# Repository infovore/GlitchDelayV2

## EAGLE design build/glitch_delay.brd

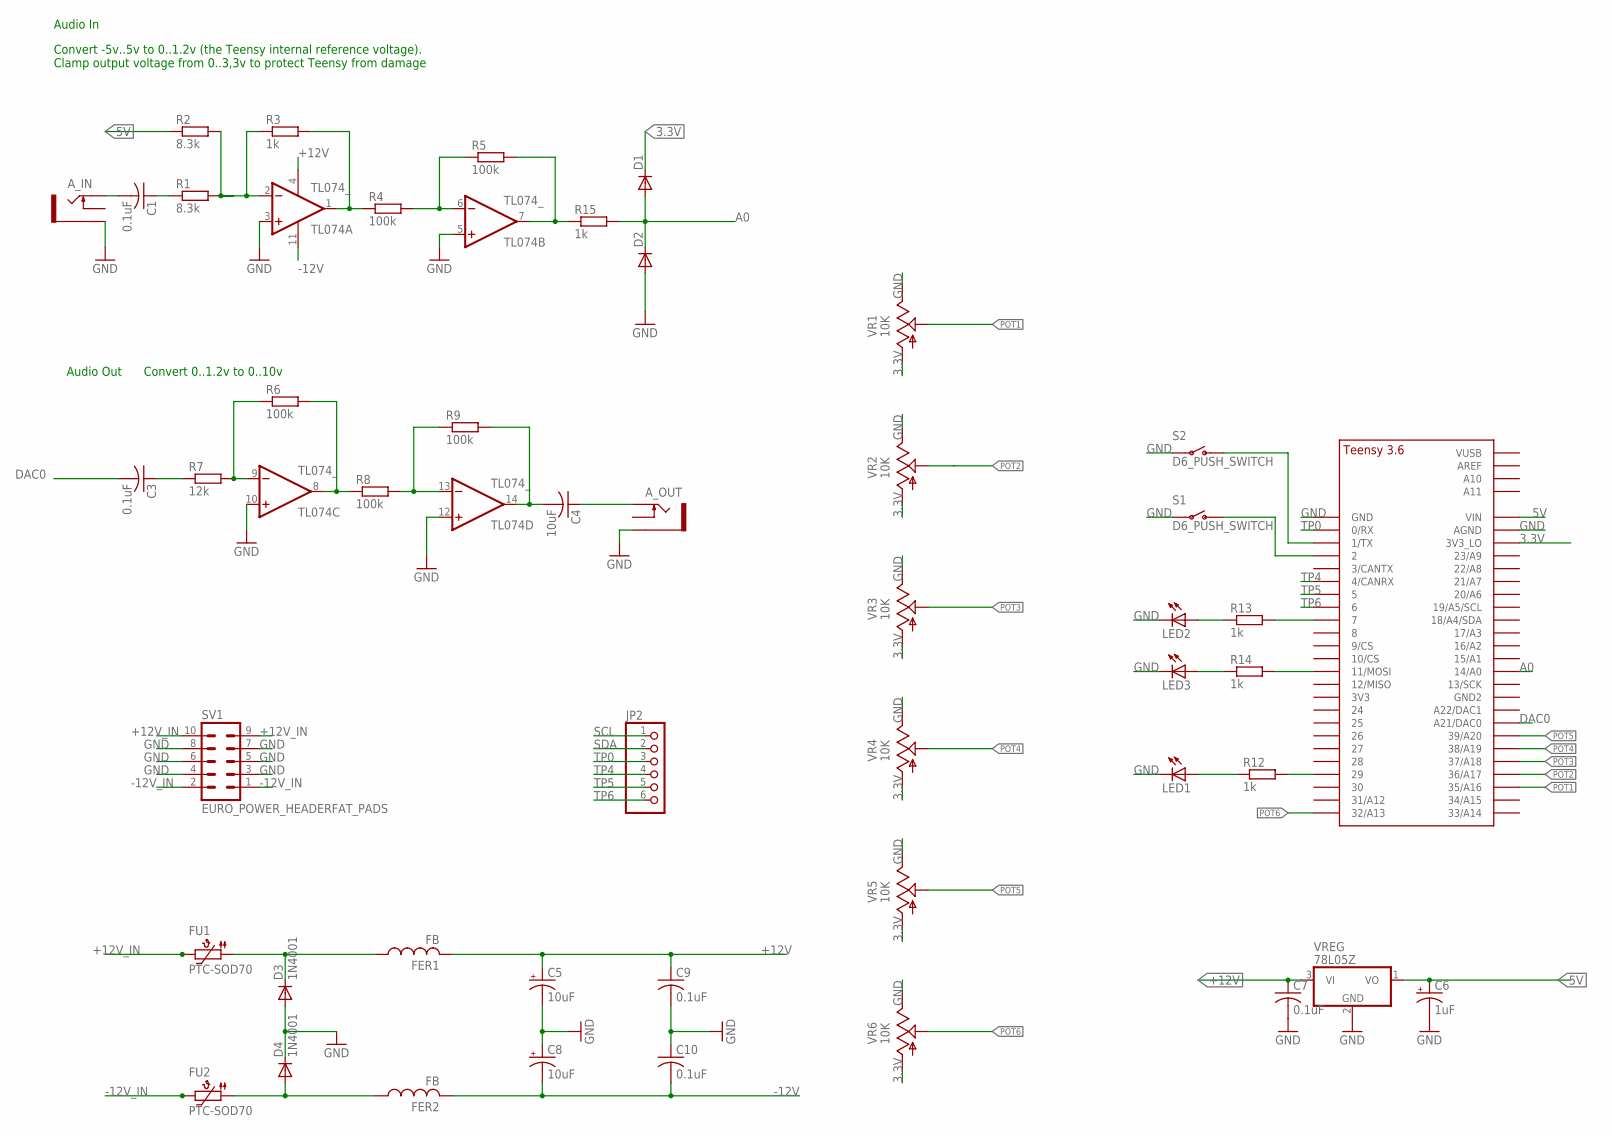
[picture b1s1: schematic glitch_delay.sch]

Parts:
A_IN: THONKICONNNEW; WQP-PJ301M-12_JACK
A_OUT: THONKICONNNEW; WQP-PJ301M-12_JACK
C1, C3, C7, C9, C10: 0.1uF; C025-030X050
C4: 10uF; C025-030X050
C5, C8: 10uF; E2,5-6E
C6: 1uF; E2,5-7
D1, D2: SMALL_DIODEDO35-7; DO35-7
D3, D4: 1N4001; DO41-10
FER1, FER2: FB
FU1, FU2: PTC-SOD70; SOD70
JP2: PINHD-1X6; 1X06
LED1, LED2, LED3: LED3MM
R1, R2: 8.3k; 7MM_RESISTOR
R3, R12, R13, R14, R15: 1k; 7MM_RESISTOR
R4, R5, R6, R8, R9: 100k; 7MM_RESISTOR
R7: 12k; 7MM_RESISTOR
S1, S2: D6_PUSH_SWITCH
SV1: EURO_POWER_HEADERFAT_PADS; EURO_PWR_HEADER_FAT
TL074: TL074_; DIL14
U$1: TEENSY_3.5/3.6_BASIC
VR1, VR2, VR3, VR4, VR5, VR6: 10K; 9MM_SNAP-IN_POT
VREG: 78L05Z; TO92

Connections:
3.3V: D1.C, U$1.3V3_LO, VR1.1 (A), VR2.1 (A), VR3.1 (A), VR4.1 (A), VR5.1 (A), VR6.1 (A)
5V: C6.+, R2.1, U$1.VIN, VREG.1 (VO)
+12V: C5.+, C7.1, C9.1, FER1.P$2 (2), TL074.4 (V+), VREG.3 (VI)
+12V_IN: FU1.2, SV1.9, SV1.10
-12V: C8.-, C10.2, FER2.P$2 (2), TL074.11 (V-)
-12V_IN: FU2.2, SV1.1, SV1.2
A0: D1.A, D2.C, R15.2, U$1.14/A0
DAC0: C3.2, U$1.21/DAC0 (A21/DAC0)
GND: A_IN.P$3_SLEEVE (SLEEVE), A_OUT.P$3_SLEEVE (SLEEVE), C5.-, C6.-, C7.2, C8.+, C9.2, C10.1, D2.A, D3.A, D4.C, LED1.K (C), LED2.K (C), LED3.K (C), S1.P$3, S1.P$4, S2.P$3, S2.P$4, SV1.3, SV1.4, SV1.5, SV1.6, SV1.7, SV1.8, TL074.3 (+IN), TL074.5 (+IN), TL074.10 (+IN), TL074.12 (+IN), U$1.AGND, U$1.GND, VR1.3 (E), VR2.3 (E), VR3.3 (E), VR4.3 (E), VR5.3 (E), VR6.3 (E), VREG.2 (GND)
unnamed: A_IN.P$1_TIP (TIP), C1.2
unnamed: R1.2, R2.2, R3.1, TL074.2 (-IN)
unnamed: R3.2, R4.1, TL074.1 (OUT)
unnamed: R4.2, R5.1, TL074.6 (-IN)
unnamed: C1.1, R1.1
unnamed: R5.2, R15.1, TL074.7 (OUT)
unnamed: LED1.A, R12.1
unnamed: C3.1, R7.1
unnamed: R6.1, R7.2, TL074.9 (-IN)
unnamed: R6.2, R8.1, TL074.8 (OUT)
unnamed: R12.2, U$1.29
unnamed: R8.2, R9.1, TL074.13 (-IN)
unnamed: LED2.A, R13.1
unnamed: S1.P$1 (O), S1.P$2 (O), U$1.2
unnamed: C4.2, R9.2, TL074.14 (OUT)
unnamed: A_OUT.P$1_TIP (TIP), C4.1
unnamed: LED3.A, R14.1
unnamed: S2.P$1 (O), S2.P$2 (O), U$1.1/TX
unnamed: R13.2, U$1.7
unnamed: R14.2, U$1.11/MOSI
unnamed: D3.C, FER1.P$1 (1), FU1.1
unnamed: D4.A, FER2.P$1 (1), FU2.1
POT1: U$1.35/A16, VR1.2 (S)
POT2: U$1.36/A17, VR2.2 (S)
POT3: U$1.37/A18, VR3.2 (S)
POT4: U$1.38/A19, VR4.2 (S)
POT5: U$1.39/A20, VR5.2 (S)
POT6: U$1.32/A13, VR6.2 (S)
SCL: JP2.1
SDA: JP2.2
TP0: JP2.3, U$1.0/RX
TP4: JP2.4, U$1.4/CANRX
TP5: JP2.5, U$1.5
TP6: JP2.6, U$1.6

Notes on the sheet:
Audio In
Audio Out
Convert -5v..5v to 0..1.2v (the Teensy internal reference voltage). Clamp output voltage from 0..3,3v to protect Teensy from damage
Convert 0..1.2v to 0..10v

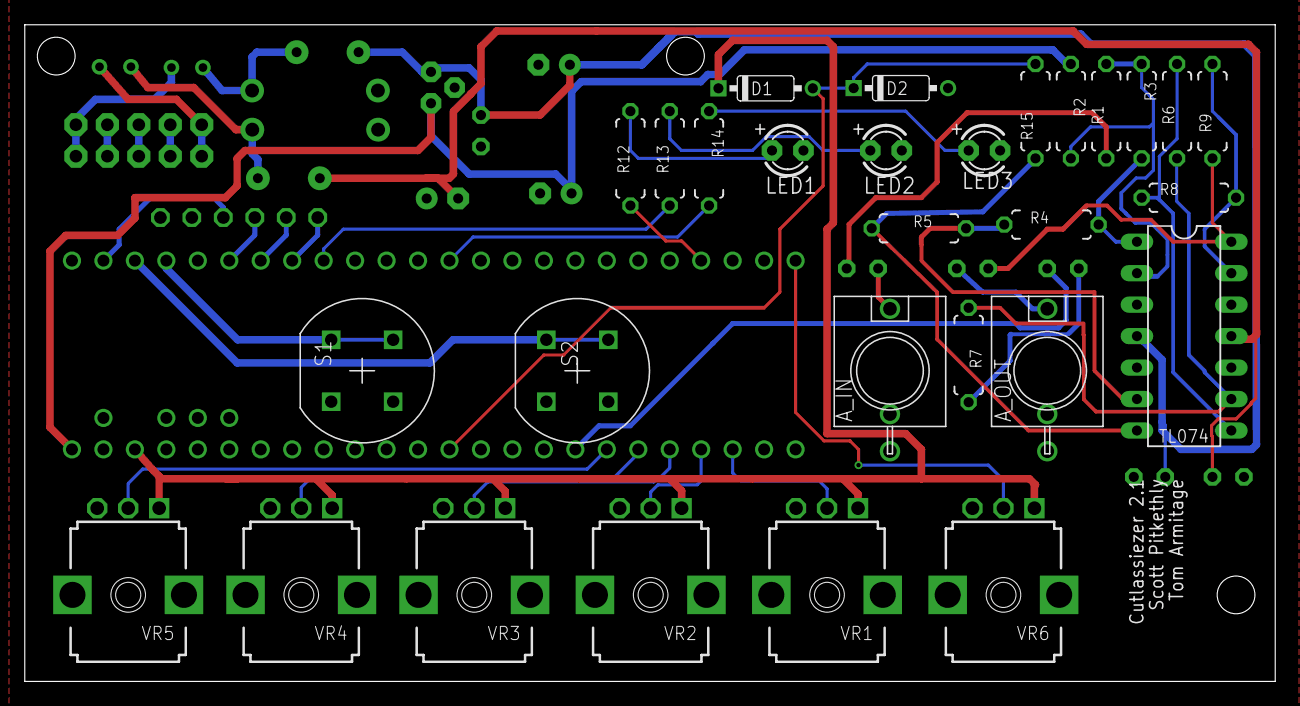
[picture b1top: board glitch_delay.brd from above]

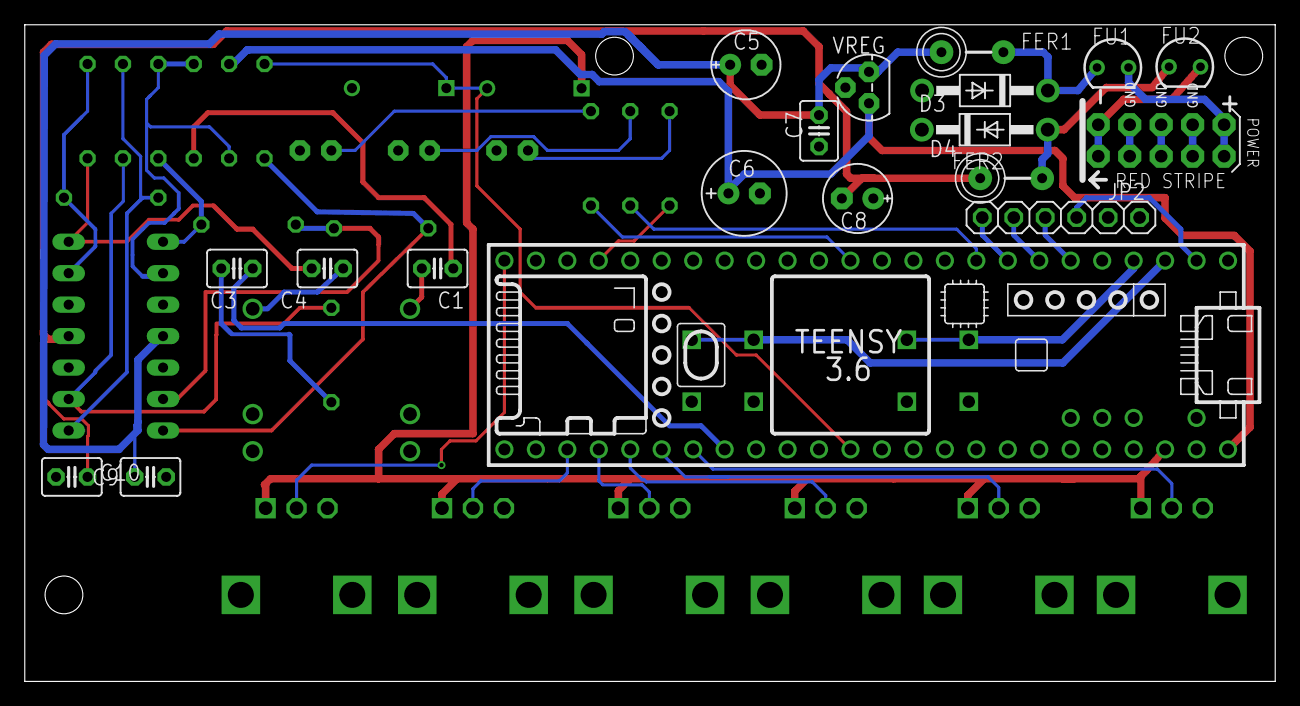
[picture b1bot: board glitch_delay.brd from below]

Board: 2 copper layers, 101.0 x 53.0 mm, 48 parts (19 on the bottom side), 41 nets.

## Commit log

2018-02-15 Removing PIC from board and using ADC1.
2018-02-15 Tearing out I2C and specifying we want to use ADC1.
2018-02-15 Minor schematic tidying.
2018-02-15 Lots of board tidying.
2018-02-15 Much smaller.
